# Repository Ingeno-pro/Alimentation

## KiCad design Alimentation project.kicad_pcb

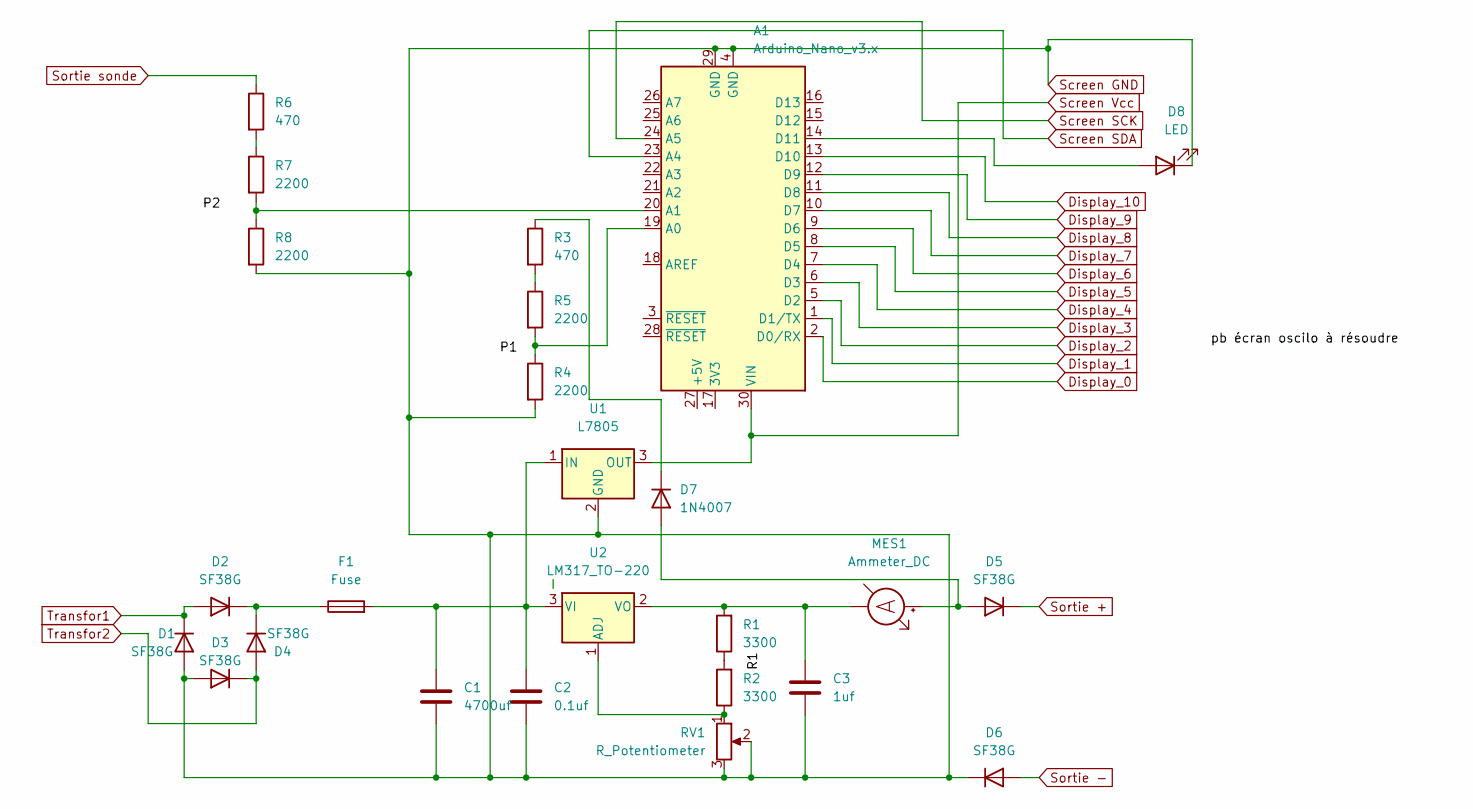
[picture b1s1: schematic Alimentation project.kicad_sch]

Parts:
A1: Arduino_Nano_v3.x; Arduino_Nano
C1: 4700uf; CP_Radial_D16.0mm_P7.50mm
C2: 0.1uf; CP_Radial_D5.0mm_P2.50mm
C3: 1uf; CP_Radial_D5.0mm_P2.50mm
D1, D2, D3, D4, D5, D6: SF38G; D_DO-201AD_P15.24mm_Horizontal
D7: 1N4007; D_DO-41_SOD81_P12.70mm_Horizontal
D8: LED; LED_D5.0mm
F1: Fuse; Fuse_0402_1005Metric
MES1: Ammeter_DC; PinHeader_1x02_P2.54mm_Vertical
R1, R2: 3300; R_Axial_DIN0207_L6.3mm_D2.5mm_P15.24mm_Horizontal
R3, R6: 470; R_Axial_DIN0207_L6.3mm_D2.5mm_P15.24mm_Horizontal
R4, R5, R7, R8: 2200; R_Axial_DIN0207_L6.3mm_D2.5mm_P15.24mm_Horizontal
RV1: R_Potentiometer; PinHeader_1x03_P2.54mm_Vertical
U1: L7805; TO-220-3_Vertical
U2: LM317_TO-220; TO-220-3_Vertical

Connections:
Display_0: A1.2 (D0/RX)
Display_1: A1.1 (D1/TX)
Display_2: A1.5 (D2)
Display_3: A1.6 (D3)
Display_4: A1.7 (D4)
Display_5: A1.8 (D5)
Display_6: A1.9 (D6)
Display_7: A1.10 (D7)
Display_8: A1.11 (D8)
Display_9: A1.12 (D9)
Display_10: A1.13 (D10)
unnamed: A1.14 (D11), D8.2 (A)
unnamed: A1.19 (A0), R4.1, R5.2
unnamed: A1.20 (A1), R7.2, R8.1
unnamed: C1.1, C2.1, F1.2, U1.1 (IN), U2.3 (VI)
unnamed: C3.1, MES1.1 (-), R1.2, U2.2 (VO)
unnamed: D2.1 (K), D4.1 (K), F1.1
unnamed: D5.2 (A), D7.2 (A), MES1.2 (+)
unnamed: R1.1, R2.2
unnamed: R2.1, RV1.1, U2.1 (ADJ)
unnamed: D7.1 (K), R3.1
unnamed: R3.2, R5.1
unnamed: R6.2, R7.1
Screen GND: A1.4 (GND), A1.29 (GND), C1.2, C2.2, C3.2, D1.2 (A), D3.2 (A), D6.1 (K), D8.1 (K), R4.2, R8.2, RV1.2, RV1.3, U1.2 (GND)
Screen SCK: A1.24 (A5)
Screen SDA: A1.23 (A4)
Screen Vcc: A1.30 (VIN), U1.3 (OUT)
Sortie +: D5.1 (K)
Sortie -: D6.2 (A)
Sortie sonde: R6.1
Transfor1: D1.1 (K), D2.2 (A)
Transfor2: D3.1 (K), D4.2 (A)

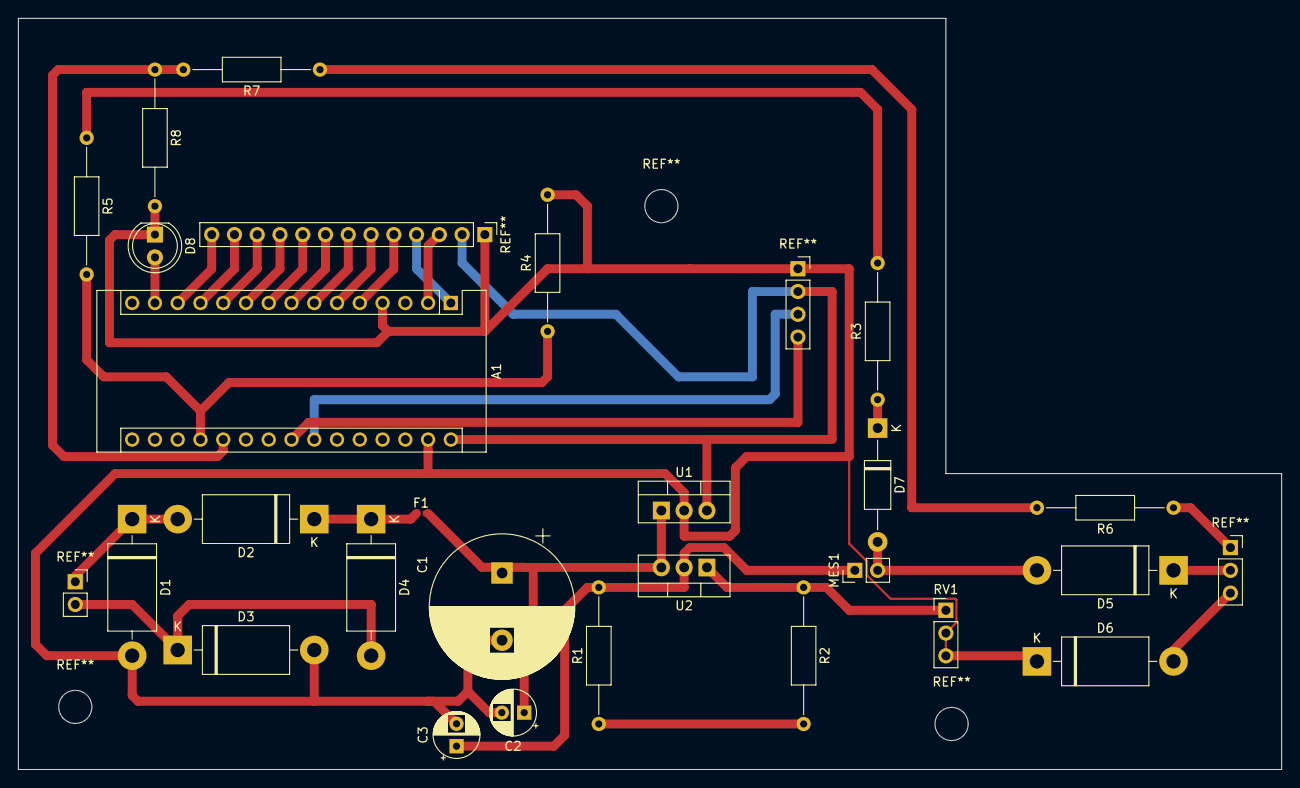
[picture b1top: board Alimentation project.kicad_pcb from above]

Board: 2 copper layers, 141.0 x 83.8 mm, 25 parts (0 on the bottom side), 16 nets.
